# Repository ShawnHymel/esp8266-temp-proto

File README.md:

ESP8266 Temperature Sensor Prototype
====================================

This is a quick prototype designed for the Bantam Tools Desktop PCB Milling Machine. It uses an ESP8266-WROOM-02 module connected to an MCP9808 temperature sensor. It will run off a single-cell LiPo battery, but there is no protection, undervoltage detection, or charge circuitry onboard. The idea is simple: read from temperature sensor and post to a server at regular intervals. It should work as a simple, IoT Temperature Sensor Throwie.

To Build
--------

Schematic found at *Hardware/esp8266-temp-sensor-schematic.pdf*.

Gerbers are found in the *Hardware/gerbers* folder. Mill them or send them off to a PCB fab house. If you want solder mask and silk screen, you'll have to run your own Gerbers from within KiCad. Also, I didn't move the REFDES labels around to make them look nice (since I was making this board on a mill). You'll probably want to do that, too.

Bill of Materials (BOM) is *Hardware/esp8266-temp-proto_BOM.xlsx*. Buy stuff listed in that. Assemble board.

To Program ESP8266
------------------

Connect 3.3V USB-to-Serial adapter to header on board:

| USB-to-Serial | ESP8266 Board |
| ------------- | ------------- |
|     3.3 V     |     3.3 V     |
|      GND      |      GND      |
|       TX      |       RX      |
|       RX      |       TX      |

Press and hold both buttons. Release RESET button first for 1 second and then release PROG button. This will put the ESP8266 into programming/bootloader mode.

Add `http://arduino.esp8266.com/stable/package_esp8266com_index.json` to the Additional Boards Manager URLs in *File > Preferences in Arduino*. Install *esp8266 by ESP8266 Community* in Boards Manager.

Open *Firmware/esp8266-temp-get/esp8266-temp-get.ino* and change SSID and WiFi password to your network's credentials. Change `hostname` to your computer's IP address. Upload to ESP8266-WROOM-02.

To Run Server
-------------

Install Python (this was tested on Python 3.7). Run *Software/test-srever.py*. With your server running and ESP8266 powered, you should see temperature posted every ~10 seconds.

LED Blink Codes
---------------

Slow blink: Connecting to WiFi

Fast blink: Error

Steady on: Posting to server

License
-------

The hardware (schematic and PCB layout) is licensed under Creative Commons 4.0 BY [CC BY 4.0](https://creativecommons.org/licenses/by/4.0/).

The software (Arduino and Python code found in Firmware/ and Software/) is [Beerware](https://en.wikipedia.org/wiki/Beerware).

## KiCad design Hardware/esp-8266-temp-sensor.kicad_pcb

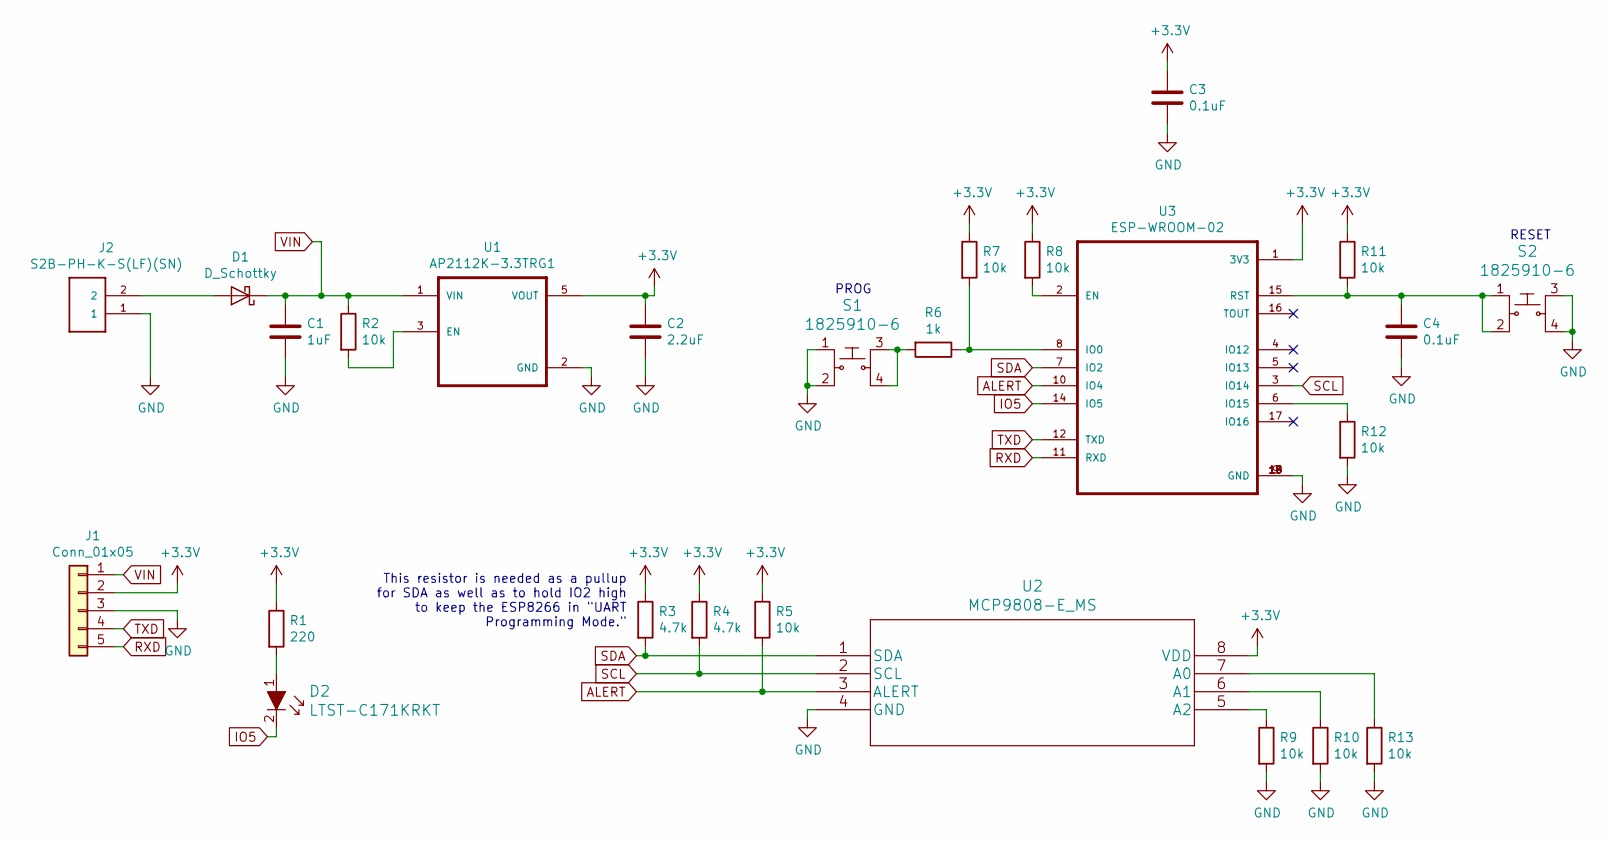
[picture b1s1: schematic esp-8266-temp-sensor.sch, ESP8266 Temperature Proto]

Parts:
C1: 1uF; C_0805_2012Metric_Pad1.15x1.40mm_HandSolder
C2: 2.2uF; C_0805_2012Metric_Pad1.15x1.40mm_HandSolder
C3, C4: 0.1uF; C_0805_2012Metric_Pad1.15x1.40mm_HandSolder
D1: D_Schottky; D_SOD-123F
D2: LTST-C171KRKT; 0805; MPN LTST-C171KRKT; Digi-Key_PN 160-1427-1-ND
J1: Conn_01x05; PinSocket_1x05_P2.54mm_Vertical_SMD_Pin1Left
J2: S2B-PH-K-S(LF)(SN); JST_S2B-PH-K-S(LF)(SN)
R1: 220; R_0805_2012Metric_Pad1.15x1.40mm_HandSolder
R2, R5, R7, R8, R9, R10, R11, R12, R13: 10k; R_0805_2012Metric_Pad1.15x1.40mm_HandSolder
R3, R4: 4.7k; R_0805_2012Metric_Pad1.15x1.40mm_HandSolder
R6: 1k; R_0805_2012Metric_Pad1.15x1.40mm_HandSolder
S1, S2: 1825910-6; Switch_Tactile_THT_6x6mm; MPN 1825910-6; Digi-Key_PN 450-1650-ND
U1: AP2112K-3.3TRG1; SOT95P285X140-5N
U2: MCP9808-E_MS; MCP9808-E&slash_MS
U3: ESP-WROOM-02; MODULE_ESP-WROOM-02

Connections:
+3V3: C2.1, C3.1, J1.2, R1.1, R3.1, R4.1, R5.1, R7.1, R8.1, R11.1, U1.5 (VOUT), U2.8 (VDD), U3.1 (3V3)
ALERT: R5.2, U2.3 (ALERT), U3.10 (IO4)
GND: C1.2, C2.2, C3.2, C4.2, J1.3, J2.1, R9.2, R10.2, R12.2, R13.2, S1.1, S1.2, S2.3, S2.4, U1.2 (GND), U2.4 (GND), U3.9 (GND), U3.13 (GND), U3.18 (GND), U3.19 (GND)
IO5: D2.2, U3.14 (IO5)
unnamed: C4.1, R11.2, S2.1, S2.2, U3.15 (RST)
unnamed: D1.2 (A), J2.2
unnamed: D2.1, R1.2
unnamed: R2.2, U1.3 (EN)
unnamed: R6.1, R7.2, U3.8 (IO0)
unnamed: R6.2, S1.3, S1.4
unnamed: R8.2, U3.2 (EN)
unnamed: R9.1, U2.5 (A2)
unnamed: R10.1, U2.6 (A1)
unnamed: R12.1, U3.6 (IO15)
unnamed: R13.1, U2.7 (A0)
RXD: J1.5, U3.11 (RXD)
SCL: R4.2, U2.2 (SCL), U3.3 (IO14)
SDA: R3.2, U2.1 (SDA), U3.7 (IO2)
TXD: J1.4, U3.12 (TXD)
VIN: C1.1, D1.1 (K), J1.1, R2.1, U1.1 (VIN)

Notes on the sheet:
This resistor is needed as a pullup for SDA as well as to hold IO2 high to keep the ESP8266 in "UART Programming Mode."
PROG
RESET

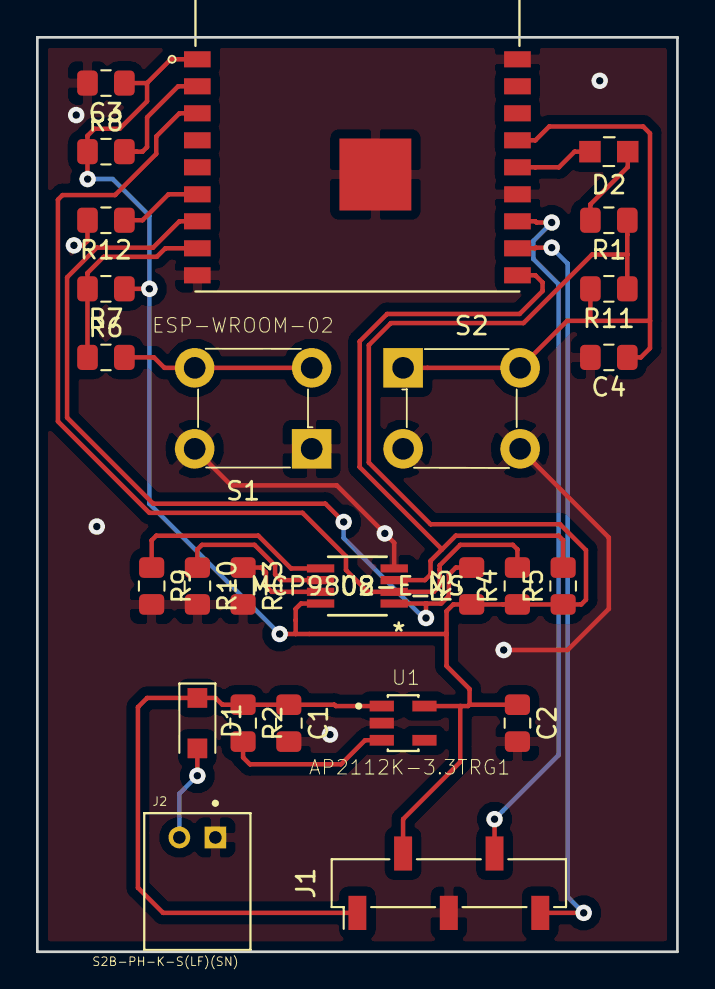
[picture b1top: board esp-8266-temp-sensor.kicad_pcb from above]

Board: 2 copper layers, 35.6 x 50.8 mm, 26 parts (0 on the bottom side), 20 nets.

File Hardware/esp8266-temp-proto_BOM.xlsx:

Reference | Quantity | Value | Footprint | MPN | Price | Total Price | Part Page
C1 | 1 | 1uF | Capacitor_SMD:C_0805_2012Metric_Pad1.15x1.40mm_HandSolder | 08053C105KAT2A | 0.28999999999999998 | 0.28999999999999998 | https://www.digikey.com/product-detail/en/avx-corporation/08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
C2 | 1 | 2.2uF | Capacitor_SMD:C_0805_2012Metric_Pad1.15x1.40mm_HandSolder | 08053C225K4Z2A | 0.47 | 0.47 | https://www.digikey.com/product-detail/en/avx-corporation/08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
C3 C4 | 2 | 0.1uF | Capacitor_SMD:C_0805_2012Metric_Pad1.15x1.40mm_HandSolder | 08055C104KAT2A | 0.22 | 0.44 | https://www.digikey.com/product-detail/en/avx-corporation/08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
D1 | 1 | D_Schottky | Diode_SMD:D_SOD-123F | MBR120VLSFT3G | 0.42 | 0.42 | https://www.digikey.com/product-detail/en/on-semiconductor/M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
D2 | 1 | LTST-C171KRKT | digikey-footprints:0805 | LTST-C171KRKT | 0.31 | 0.31 | https://www.digikey.com/product-detail/en/lite-on-inc/LTST-C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
J1 | 1 | Conn_01x05 | Connector_PinSocket_2.54mm:PinSocket_1x05_P2.54mm_Vertical_SMD_Pin1Left | NPTC051KFXC-RC | 0.86 | 0.86 | https://www.digikey.com/product-detail/en/sullins-connector-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
J2 | 1 | S2B-PH-K-S(LF)(SN) | S2B-PH-K-S_LF__SN_:JST_S2B-PH-K-S(LF)(SN) | S2B-PH-K-S(LF)(SN) | 0.17 | 0.17 | https://www.digikey.com/product-detail/en/jst-sales-america-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
R1 | 1 | 220 | Resistor_SMD:R_0805_2012Metric_Pad1.15x1.40mm_HandSolder | RC0805FR-07220RL | 0.1 | 0.1 | https://www.digikey.com/product-detail/en/yageo/RC0805FR-072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
R10 R11 R12 R13 R2 R5 R7 R8 R9 | 9 | 10k | Resistor_SMD:R_0805_2012Metric_Pad1.15x1.40mm_HandSolder | RC0805FR-0710KL | 0.1 | 0.9 | https://www.digikey.com/product-detail/en/yageo/RC0805FR-071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
R3 R4 | 2 | 4.7k | Resistor_SMD:R_0805_2012Metric_Pad1.15x1.40mm_HandSolder | RC0805FR-074K7L | 0.1 | 0.2 | https://www.digikey.com/product-detail/en/yageo/RC0805FR-074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
R6 | 1 | 1k | Resistor_SMD:R_0805_2012Metric_Pad1.15x1.40mm_HandSolder | RC0805FR-071KL | 0.1 | 0.1 | https://www.digikey.com/product-detail/en/yageo/RC0805FR-071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
S1 S2 | 2 | 1825910-6 | digikey-footprints:Switch_Tactile_THT_6x6mm | 1825910-6 | 0.11 | 0.22 | https://www.digikey.com/product-detail/en/te-connectivity-al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
U1 | 1 | AP2112K-3.3TRG1 | AP2112K-3.3TRG1:SOT95P285X140-5N | AP2112K-3.3TRG1 | 0.49 | 0.49 | https://www.digikey.com/product-detail/en/diodes-incorporate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
U2 | 1 | MCP9808-E_MS | MCP9808-E&slash_MS:MCP9808-E&slash_MS | MCP9808-E/MS | 1.1599999999999999 | 1.1599999999999999 | https://www.digikey.com/product-detail/en/microchip-technolo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
U3 | 1 | ESP-WROOM-02 | ESP-WROOM-02:MODULE_ESP-WROOM-02 | ESP-WROOM-02 | 2.7 | 2.7 | https://www.digikey.com/product-detail/en/espressif-systems/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
 |  |  |  |  | Total: | 8.83

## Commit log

2019-02-24 Layout and software complete
2019-02-24 Updated README again
2019-02-24 Fixed README
2019-02-24 Fixed README again

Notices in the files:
Hardware/esp-8266-temp-sensor.sch:
License: CC BY 4.0
parts and their libraries:
Copyright 2016 Accelerated Designs. All rights reserved.
